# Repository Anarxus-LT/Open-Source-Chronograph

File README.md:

# Open-Source-Chronograph
 An open source chronograph used to measure the speed and energy of projectiles. Mainly intended for airsoft.

>[!CAUTION]
>**SOME DISPLAYS HAVE INVERTED GND AND VCC!!!**\
>I have added jumpers for both versions
>
>ToDo: upload photos with examples
>= FOR PIN 1 GND X FOR PIN 1 VCC

## Donations :smiley:
Did you find the project useful ? feel free to buy me a cofee :coffee:

No hard feeling if you dont :wink:

## Firmware Instructions
ToDo: change file name?
To upload the firmware to the pi pico
1. Unplug the usb cable
2. Press the "BOOTSEL" button and hold it
3. Plug the usb cable
4. Copy the "Open_Source_chronograph.ino.uf2" to the drive that showed up

## Components used
ToDo: needs updating
* TP4056 module with BMS
* 18650 battery
* 1x small power switch  (I used a generic 10x15mm switch)
* SSD1306 128x64 I2C OLED display
* Pi pico with headers soldered
* 4pin right angle male header
* 2x 20pin female headers
* 5v buzzer
* 3 tactile switches
* 2 IR LEDs (and appropriete resistors)
* 1A fuse

## Print settings
ToDo

## Assembly notes?
ToDo

## PCB
Should be easy to do on a protoboard
Created proper PCB that you can send to your prefered PCB manufacturer

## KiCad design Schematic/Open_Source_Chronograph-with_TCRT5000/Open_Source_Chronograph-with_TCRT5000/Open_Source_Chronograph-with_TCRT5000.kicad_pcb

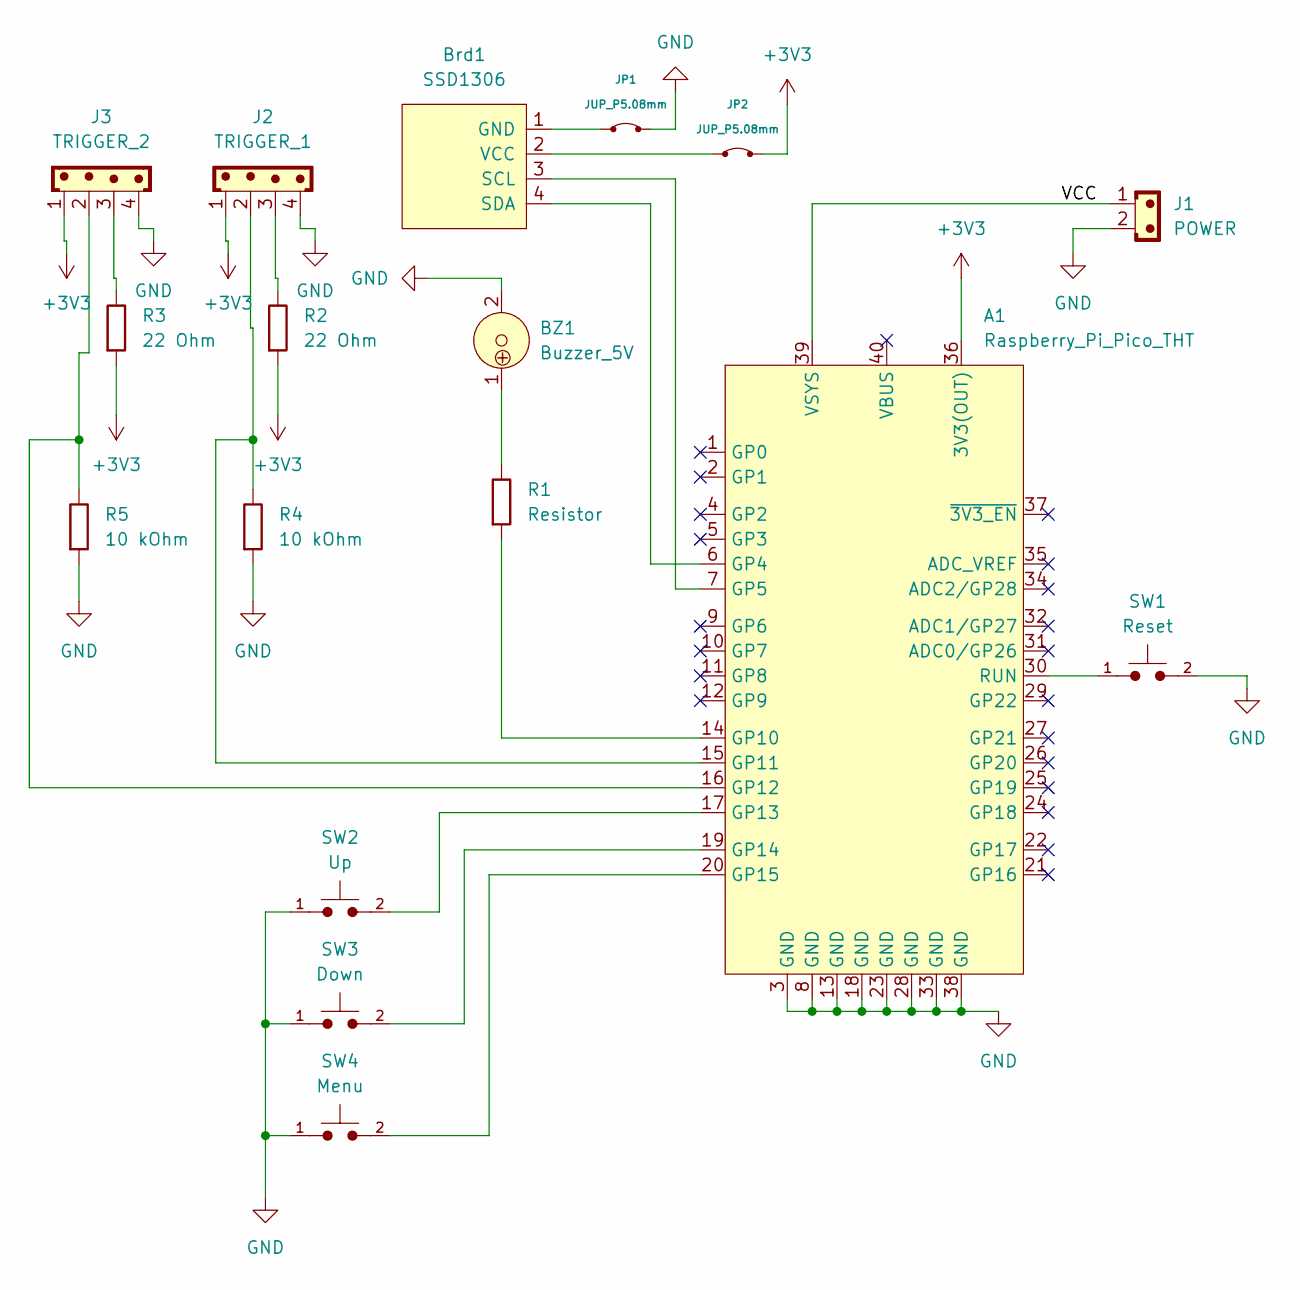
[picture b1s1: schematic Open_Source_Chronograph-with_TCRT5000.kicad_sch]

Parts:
A1: Raspberry_Pi_Pico_THT; raspberry_pi_pico_THT
BZ1: Buzzer_5V; MagneticBuzzer_ProSignal_ABT-410-RC
Brd1: SSD1306; JST_EH_B4B-EH-A_1x04_P2.50mm_Vertical
J1: POWER; JST_PH_B2B-PH-K_1x02_P2.00mm_Vertical
J2: TRIGGER_1; JST_PH_B4B-PH-K_1x04_P2.00mm_Vertical
J3: TRIGGER_2; JST_PH_B4B-PH-K_1x04_P2.00mm_Vertical
JP1, JP2: JUP_P5.08mm
R1: Resistor; R_Axial_DIN0207_L6.3mm_D2.5mm_P10.16mm_Horizontal
R2, R3: 22 Ohm; R_Axial_DIN0207_L6.3mm_D2.5mm_P10.16mm_Horizontal
R4, R5: 10 kOhm; R_Axial_DIN0207_L6.3mm_D2.5mm_P10.16mm_Horizontal
SW1: Reset; SW_PUSH_6mm_multipin
SW2: Up; SW_PUSH_6mm_multipin
SW3: Down; SW_PUSH_6mm_multipin
SW4: Menu; SW_PUSH_6mm_multipin

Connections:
+3V3: A1.36 (3V3(OUT)), J2.1, J3.1, JP2.2, R2.1, R3.1
/VCC: A1.39 (VSYS), J1.1
GND: A1.3 (GND), A1.8 (GND), A1.13 (GND), A1.18 (GND), A1.23 (GND), A1.28 (GND), A1.33 (GND), A1.38 (GND), BZ1.2, J1.2, J2.4, J3.4, JP1.2, R4.1, R5.1, SW1.2, SW2.1, SW3.1, SW4.1
unnamed: A1.6 (GP4), Brd1.4 (SDA)
unnamed: A1.7 (GP5), Brd1.3 (SCL)
unnamed: A1.14 (GP10), R1.1
unnamed: A1.15 (GP11), J2.2, R4.2
unnamed: A1.16 (GP12), J3.2, R5.2
unnamed: A1.17 (GP13), SW2.2
unnamed: A1.19 (GP14), SW3.2
unnamed: A1.20 (GP15), SW4.2
unnamed: A1.30 (RUN), SW1.1
unnamed: BZ1.1, R1.2
unnamed: Brd1.1 (GND), JP1.1
unnamed: Brd1.2 (VCC), JP2.1
unnamed: J2.3, R2.2
unnamed: J3.3, R3.2

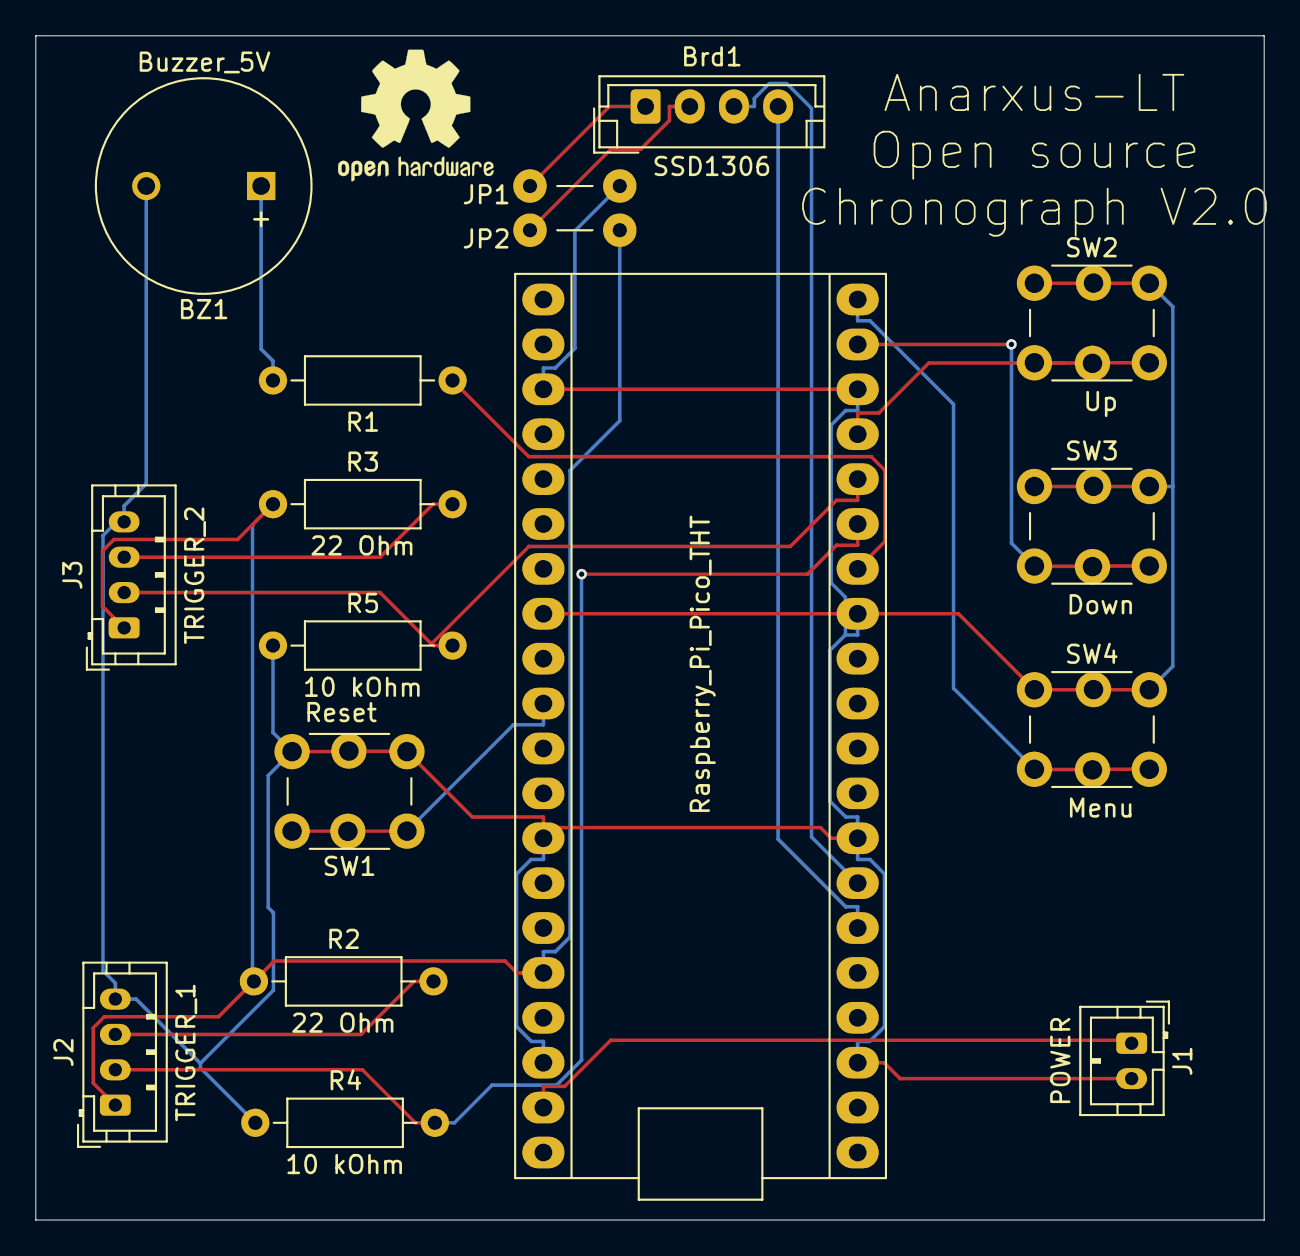
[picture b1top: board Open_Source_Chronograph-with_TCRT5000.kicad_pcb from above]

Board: 2 copper layers, 69.5 x 67.0 mm, 17 parts (0 on the bottom side), 17 nets.

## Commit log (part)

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2024-03-18 Filename update
2024-03-18 Created required directories for Arduino IDE
2024-03-18 Added trigger handling
2024-03-19 Feature implementation
    Added metric speed, power and rps functions. Waiting for ir parts to create the triggers
2024-03-20 Added buzzer functionality
2024-03-20 Started schematic design
2024-03-21 Continued schematic
2024-03-21 KiCad schematics
    Trying KiCad because i did not like eagle
2024-03-22 Schematic update
    Removed Eagle CAD schematics and recreated with KiCAD.
    Triggers will be implemented when IR LEDs arrive
2024-03-26 Schematic update & firmware testing
    Expected phototransistors, got photodiodes. I created a second schematic and i will add transistors to the photodiodes.
    Doing tests
2024-03-27 Trigger testing and settings
    Everything seems to be working. The photodiode seems to have a narrow detection field. Might have to design a way to allign the bbs.
2024-03-30 Started enclosure design and added a fuse
2024-03-30 Completed enclosure design
    The design is a basic prototype and has some issues. Should be redesigned better in the future.
2024-03-30 Created ready uf2 build
2024-03-30 Added fuse and exported schematics
2024-03-31 Updated CAD model
    Added some cosmetic changes
2024-03-31 Uploaded photos for readme
2024-04-03 Fixed bugs, rewrote trigger code
    Fixed incorrect bad read
    Fixed RPS logical error
    Rewrote the trigger code to run on the second core without interrupts for better accuracy.
    Moved UI update code to main loop and kept the same functionality.
    Tested it, results seem accurate.
2024-04-03 Compiled new binaries
2024-04-03 uploaded completed version
